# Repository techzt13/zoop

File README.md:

# ZOOP

**Zack's DIY fitness band. Your sensors. Your data.**

ZOOP is an original, Whoop-inspired experiment built around an ESP32-S3-Zero, a GY-MAX30102 optical pulse sensor and a GY-521 motion sensor. It streams an experimental heart-rate estimate over Bluetooth and pulse/motion data over USB. The goal is to understand wearable sensing using parts already on hand, rather than paying for a closed subscription.

**Design submission, not a finished build.** Dimensions for the actual modules still need measurement, and the device has not been assembled or tested on a wrist. ZOOP is independent of Whoop: it does not copy proprietary software, work with the Whoop app, or promise equivalent accuracy, battery life, sleep staging, recovery or strain scores.

## Full 3D assembly

Open the [FreeCAD assembly](cad/ZOOP_assembly.FCStd). [Assembly STEP](cad/assembly.step), individual part STEP files, modeling source, dimensions and mechanical validation details are in [cad/](cad/). Electronics are explicitly labeled reference-envelope models, not dimensionally certified supplier models.

## Electronics

The compact carrier distributes four signals to wire headers: 3.3 V, GND, SDA and SCL. It is an **alternative** to cutting and hand-wiring the owned perfboard, not a custom replacement for the sensor modules. Header numbers are carrier positions, not the modules' physical pin order.

The [KiCad project](electronics/wristband.kicad_pro), [schematic](electronics/wristband.kicad_sch), [PCB](electronics/wristband.kicad_pcb), local settings, libraries and [Gerber ZIP](electronics/gerbers.zip) are in [electronics/](electronics/README.md). The images are generated from the actual design, not build photos. Read the electrical validation and manufacturing limitations before ordering.

### Wiring

With power disconnected, wire by the **labels on your exact modules**:

| ESP32-S3-Zero | GY-MAX30102 | GY-521 |
|---|---|---|
| 3V3 | VIN/VCC, if verified 3.3 V compatible | VCC, if verified 3.3 V compatible |
| GND | GND | GND and AD0 |
| GPIO5 | SDA | SDA |
| GPIO6 | SCL | SCL |

The MAX30102 normally uses I²C address `0x57`; grounding MPU6050 AD0 selects `0x68`. Leave unused INT, XDA, XCL and other signals disconnected. The MSK-12C02 is listed as owned but **unused**: disconnect USB to turn this prototype off. Some versions are rated only 50 mA and must not switch ESP32 power directly.

**Breakout variants differ.** Inspect the actual regulators, LED supply and I²C pull-ups. SDA/SCL must not be pulled to 5 V, and the combined pull-up resistance must be suitable for the shared bus. Some GY-521 regulators will not operate reliably from a 3.3 V input. If either module cannot accept the assumed supply, revise the wiring and schematic before powering it; do not infer safety from its marketplace name.

## Build and use

1. Measure board outlines, thicknesses, header orientation, sensor position and USB plug clearance. Adjust the CAD parameters and regenerate exports before printing. Verify the actual electrical requirements above.
2. Choose **one** carrier: cut the owned perfboard to the modeled envelope, or order the checked custom PCB. Use insulated wires, trim header pins for clearance and label both ends. Check continuity and shorts with power disconnected.
3. Print and assemble using the [CAD instructions](cad/README.txt). The case has a carrier support and optical guide, but the ESP32 and GY-521 do not yet have modeled mechanical fasteners, and the optical retainer needs verification. Design and verify secure retention for all boards and the strap. The optical window must face the skin; validate retention and ambient-light shielding rather than covering the sensor lens with opaque material.
4. Compile and upload the firmware below. First test the electronics off-body on USB. Confirm both sensors initialize and that the optical stream changes when a stationary finger is placed over the lens.
5. For an experimental body-worn test, disconnect the mains-powered computer/charger and use an isolated, protected USB power bank outside the enclosure. Adjust the strap loosely enough for circulation. The current design has no internal battery or charging circuit.
6. Subscribe to ZOOP's standard BLE heart-rate service with a generic BLE client, or read USB serial for the full pulse/motion stream.

The [BOM](BOM.csv) lists candidate soldering, measuring and assembly tools; borrow them if available and request only what is needed. The existing Mac laptop is used for CAD and firmware. Printing service costs still need a quote.

## Firmware

Source: [firmware/ZOOP/ZOOP.ino](firmware/ZOOP/ZOOP.ino).

Install Arduino IDE or Arduino CLI, **Espressif ESP32 core 3.3.5**, and **SparkFun MAX3010x Pulse and Proximity Sensor Library 1.1.2**. Select the matching ESP32-S3 board and enable **USB CDC On Boot**. For a Waveshare board, follow its [Arduino instructions](https://docs.waveshare.com/ESP32-S3-Zero/Arduino). If flashing fails, use your board's BOOT/reset sequence.

The reproducible compile target used by [CI](.github/workflows/firmware.yml) is:

```sh
arduino-cli compile --fqbn esp32:esp32:esp32s3:CDCOnBoot=cdc firmware/ZOOP
```

The default generic ESP32-S3 target does not enable PSRAM; the firmware does not require it. Do not flash a different board's flash/PSRAM settings without checking your hardware.

Serial Monitor at **115200 baud** prints:

```text
ms,ir,contact,bpm,ax_g,ay_g,az_g,gx_dps,gy_dps,gz_dps
```

BPM is empty until plausible beat intervals have been collected. The starting contact threshold is uncalibrated. An optical-sampling stall or implausible interval invalidates the estimate; sensor initialization/read errors are reported explicitly. The MPU6050 scales are ±2 g and ±250 degrees/second. There is no onboard recording; save serial data on your computer if needed.

Over BLE, the device name is **ZOOP**, Heart Rate Service is `0x180D`, and Heart Rate Measurement is `0x2A37`. Enable notifications. Approximate BPM is sent about once a second when valid; no pulse estimate is sent when invalid. Your client must handle stale/absent notifications. Motion data is currently USB-only.

**BLE is unencrypted and not authenticated.** Nearby people may connect and read estimates. Use only with consent; this is not private health-data storage.

## BOM and funding

[BOM.csv](BOM.csv) lists the six owned supplies and existing laptop at **$0 requested**, and a **$163.69 provisional subtotal**, including candidate tools not yet confirmed owned, a $20 print allowance, and $2 for the optional custom PCB. The PCB is an alternative to the owned perfboard; its advertised starting price is not a quote. Retail pack sizes and linked prices are shown.

This is **not a final funding request**: the $20 allowance for printing the case, lid and optical retainer is not a quote and could be too low; shipping, tax and any extra mounting materials are also unquoted. Prices are US retail listings found on 2026-11-13, including older search-indexed listings, not live checkout quotes; confirm current prices, availability, local voltage and delivery before ordering. The caliper listing was in-store only. Confirm which tools can be borrowed and request only eligible essentials. Get a print quote after revising the design and obtain checkout totals for the destination.

The Anker power bank is an external pocket supply, not a Whoop-sized battery. Its documented trickle mode is intended for low-power devices but has not been tested with ZOOP; verify continued operation and cable clearance.

## Validation and honest limitations

Firmware has a real ESP32-S3 compile in GitHub Actions and focused host-side tests. Host tests can be reproduced with:

```sh
g++ -std=c++17 -Wall -Wextra -Werror -Itests/stubs tests/firmware_test.cpp -o /tmp/zoop-test
/tmp/zoop-test
```

The FreeCAD solids and STEP round trips passed geometric checks; KiCad 9 ERC and DRC with schematic parity passed. Details and assumptions are documented beside the sources. Passing these and the firmware compile does **not** establish physical fit, electrical compatibility, reliable wrist pulse detection, manufacturing acceptance or safe prolonged wear. Complete board retention, wire routing and exact module measurements before calling the design finished.

**Not a medical device.** Motion, light, pressure, skin contact and sensor quality can make readings wrong. Do not use ZOOP for diagnosis, treatment, exercise safety decisions or emergencies. Never wear it connected to a mains-powered charger/computer; never connect a bare LiPo directly to USB, 5V or 3V3. Insulate joints, stop if anything warms or irritates skin, and keep this non-waterproof prototype away from sweat and water.

For a design review, verify your actual modules and update dimensions and prices. Program approval and funding are determined by Fallen organizers.

For a **build submission**, add genuine finished-product photos and a real demo-video link, document measured behavior, and update every source/export to match what was built. None are fabricated here.

## References and license

- [SparkFun MAX3010x library](https://github.com/sparkfun/SparkFun_MAX3010x_Sensor_Library): the included firmware calls its `heartRate.h` beat detector; library source and licensing remain upstream.
- [MAX30102 manufacturer information](https://www.analog.com/en/products/max30102.html).
- [MPU6050 manufacturer information](https://invensense.tdk.com/products/motion-tracking/6-axis/mpu-6050/).
- [ESP32-S3-Zero documentation](https://www.waveshare.com/wiki/ESP32-S3-Zero).

Original ZOOP source and documentation are [MIT-licensed](LICENSE). Supplier/module references are credited; their trademarks and designs belong to their respective owners.

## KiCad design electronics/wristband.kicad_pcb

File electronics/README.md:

# ZOOP experimental wire-header carrier

This 44 × 18 mm custom PCB is an alternative to the hand-wired perfboard, not
an ESP32 or sensor module replacement. Each module is wired to its corresponding
header; header pin numbers are not the module pin order. No module footprints,
power switch, charger, protection circuit, battery, sensor pull-ups or mounting
holes are included. Modules and their wiring remain external to the PCB.

| Carrier header | 1 | 2 | 3 | 4 | 5 |
|---|---|---|---|---|---|
| J1: ESP32 | 3V3 | GND | GPIO5 / SDA | GPIO6 / SCL | — |
| J2: MAX30102 | 3V3-compatible input | GND | SDA | SCL | — |
| J3: GY-521 | 3V3-compatible input | GND | SDA | SCL | AD0 to GND |

Pin 1 is the square pad. Check actual breakout regulator and pull-up
configuration before connecting: inputs vary and SDA/SCL must not rise above
the ESP32's 3.3 V logic rail. Verify the combined pull-up resistance, the sensor
input supplies and ESP regulator current margin. USB powers the ESP32 only.
With power disconnected, use a multimeter to confirm all nets and no shorts.

`wristband.kicad_pro`, `.kicad_sch`, `.kicad_pcb`, `.kicad_prl`, local symbol
and footprint libraries form the KiCad project. `generate.py` regenerates the
scripted schematic, board and libraries; plots must then be regenerated.
`gerbers.zip` contains KiCad 7.0.11 copper, mask, front silkscreen, edge and
metric Excellon drill exports. The README's PCB and schematic images are
actual KiCad SVG plots.

KiCad 7 loaded both sources and exported a netlist matching the intended pins.
[CI](../.github/workflows/electronics.yml) runs KiCad 9 ERC and DRC with
schematic parity; the checks passed with zero violations and unconnected pads.
This is not a fabrication or safety sign-off: inspect the Gerbers in a viewer,
confirm manufacturer rules and validate actual connector fit before ordering.
The modules, 3.3 V assumptions and electrical/thermal safety are untested.
The alternative perfboard requires separate wiring and is not the PCB
represented by the Gerbers.

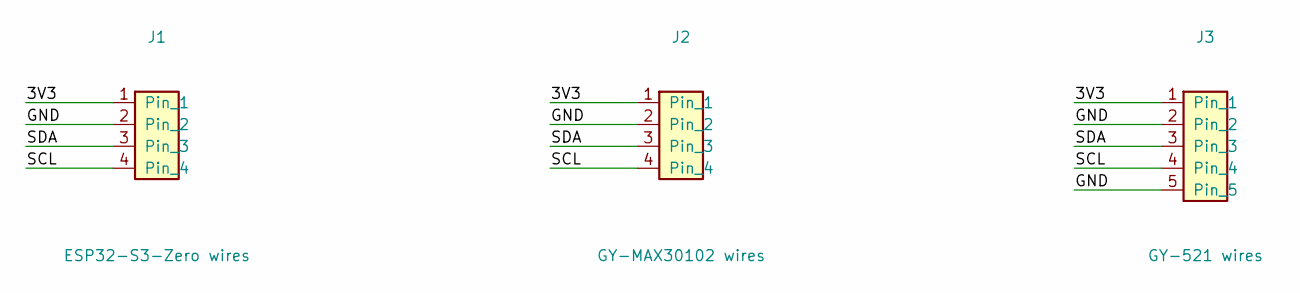
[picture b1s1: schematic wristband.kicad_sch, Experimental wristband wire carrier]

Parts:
J1: ESP32-S3-Zero wires; WireHeader_1x04_P2.54mm
J2: GY-MAX30102 wires; WireHeader_1x04_P2.54mm
J3: GY-521 wires; WireHeader_1x05_P2.54mm

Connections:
/3V3: J1.1, J2.1, J3.1
/GND: J1.2, J2.2, J3.2, J3.5
/SCL: J1.4, J2.4, J3.4
/SDA: J1.3, J2.3, J3.3

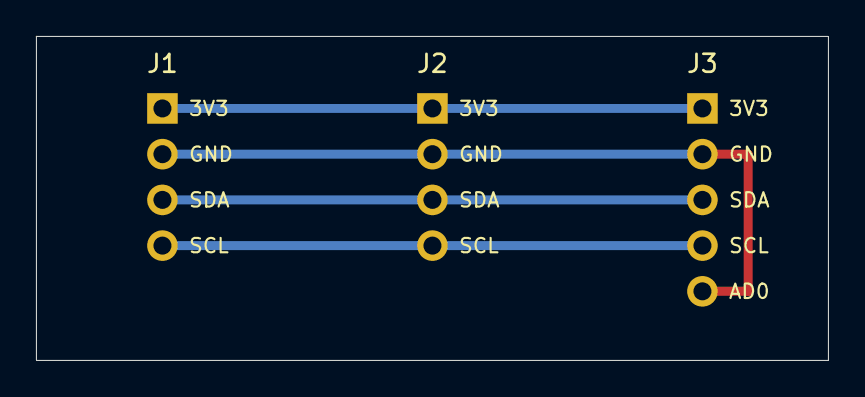
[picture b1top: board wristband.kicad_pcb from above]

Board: 2 copper layers, 44.0 x 18.0 mm, 3 parts (0 on the bottom side), 4 nets.
